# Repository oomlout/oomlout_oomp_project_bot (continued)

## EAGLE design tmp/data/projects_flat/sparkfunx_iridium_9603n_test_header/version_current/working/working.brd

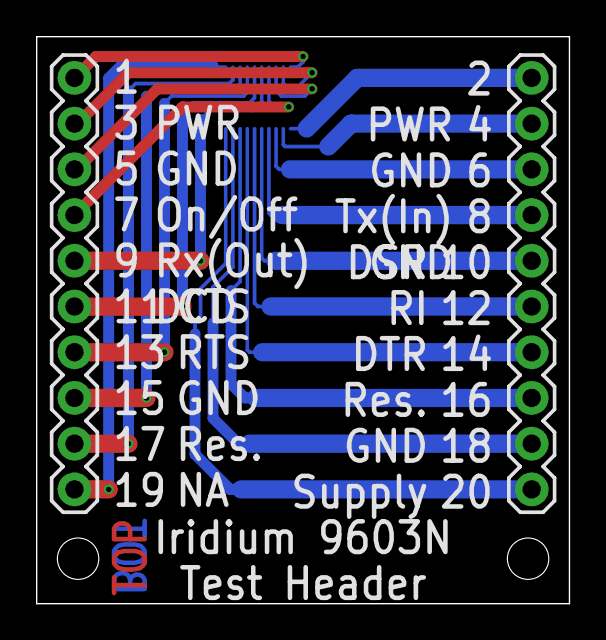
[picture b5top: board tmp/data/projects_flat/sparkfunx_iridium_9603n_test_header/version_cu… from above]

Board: 2 copper layers, 29.6 x 31.5 mm, 3 parts (1 on the bottom side), 20 nets.

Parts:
J1, J2: 1X10
J3: ST4-10-X.XX-X-D

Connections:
unnamed: J1.1, J3.1
unnamed: J2.1, J3.2
unnamed: J1.2, J3.3
unnamed: J2.2, J3.4
unnamed: J1.3, J3.5
unnamed: J2.3, J3.6
unnamed: J1.4, J3.7
unnamed: J2.4, J3.8
unnamed: J1.5, J3.9
unnamed: J2.5, J3.10
unnamed: J1.6, J3.11
unnamed: J2.6, J3.12
unnamed: J1.7, J3.13
unnamed: J2.7, J3.14
unnamed: J1.8, J3.15
unnamed: J2.8, J3.16
unnamed: J1.9, J3.17
unnamed: J2.9, J3.18
unnamed: J1.10, J3.19
unnamed: J2.10, J3.20

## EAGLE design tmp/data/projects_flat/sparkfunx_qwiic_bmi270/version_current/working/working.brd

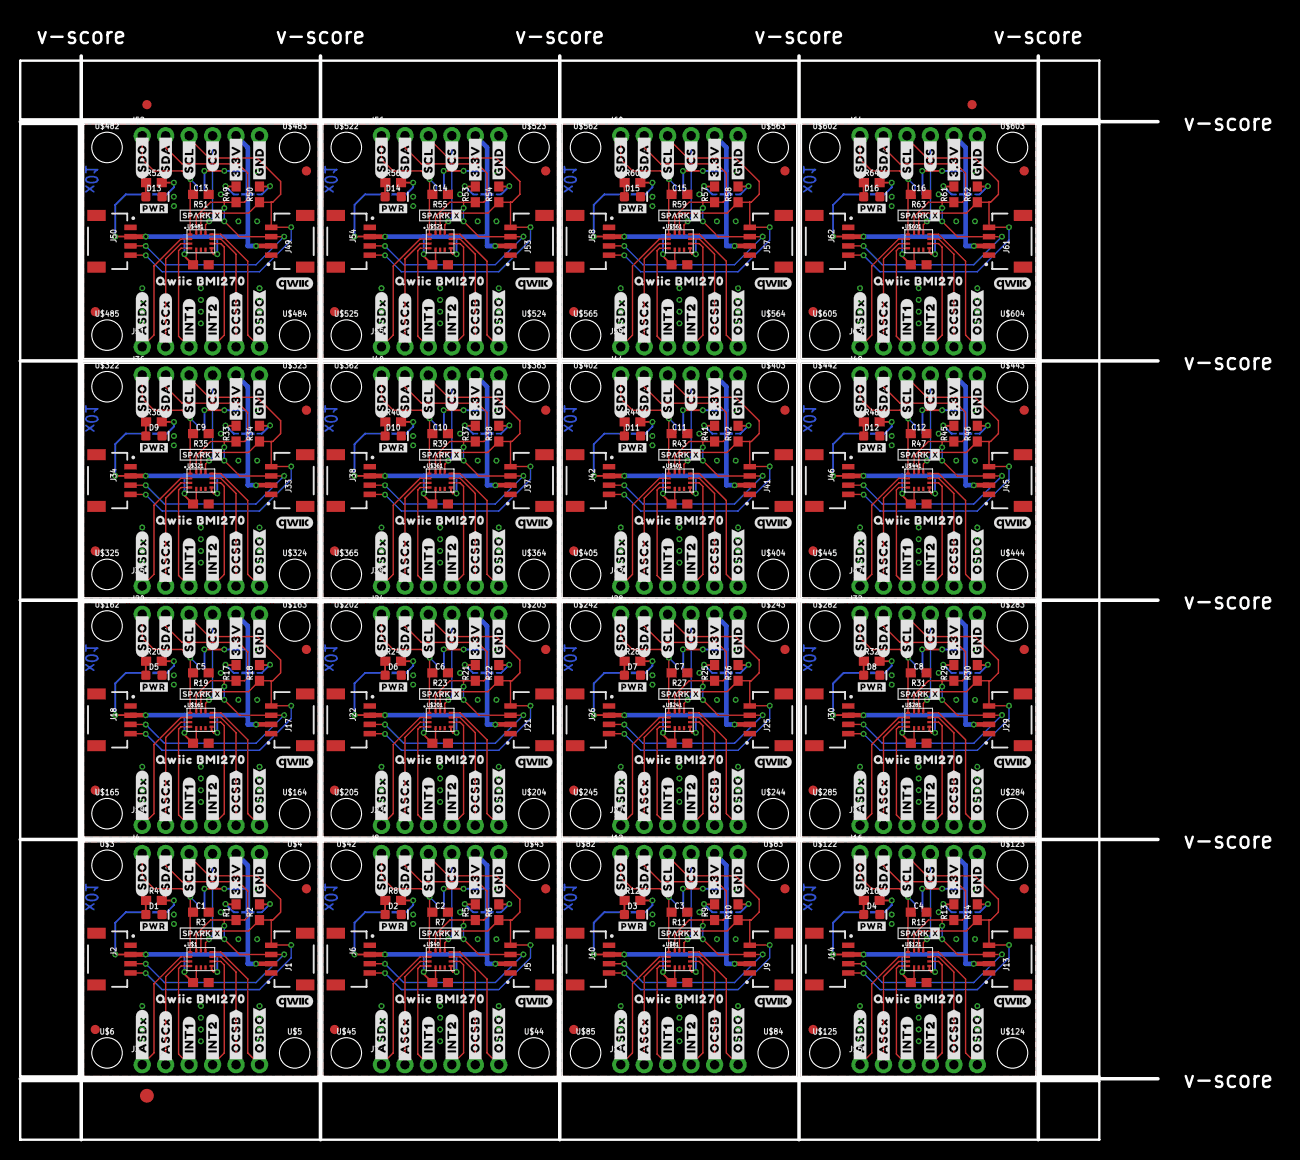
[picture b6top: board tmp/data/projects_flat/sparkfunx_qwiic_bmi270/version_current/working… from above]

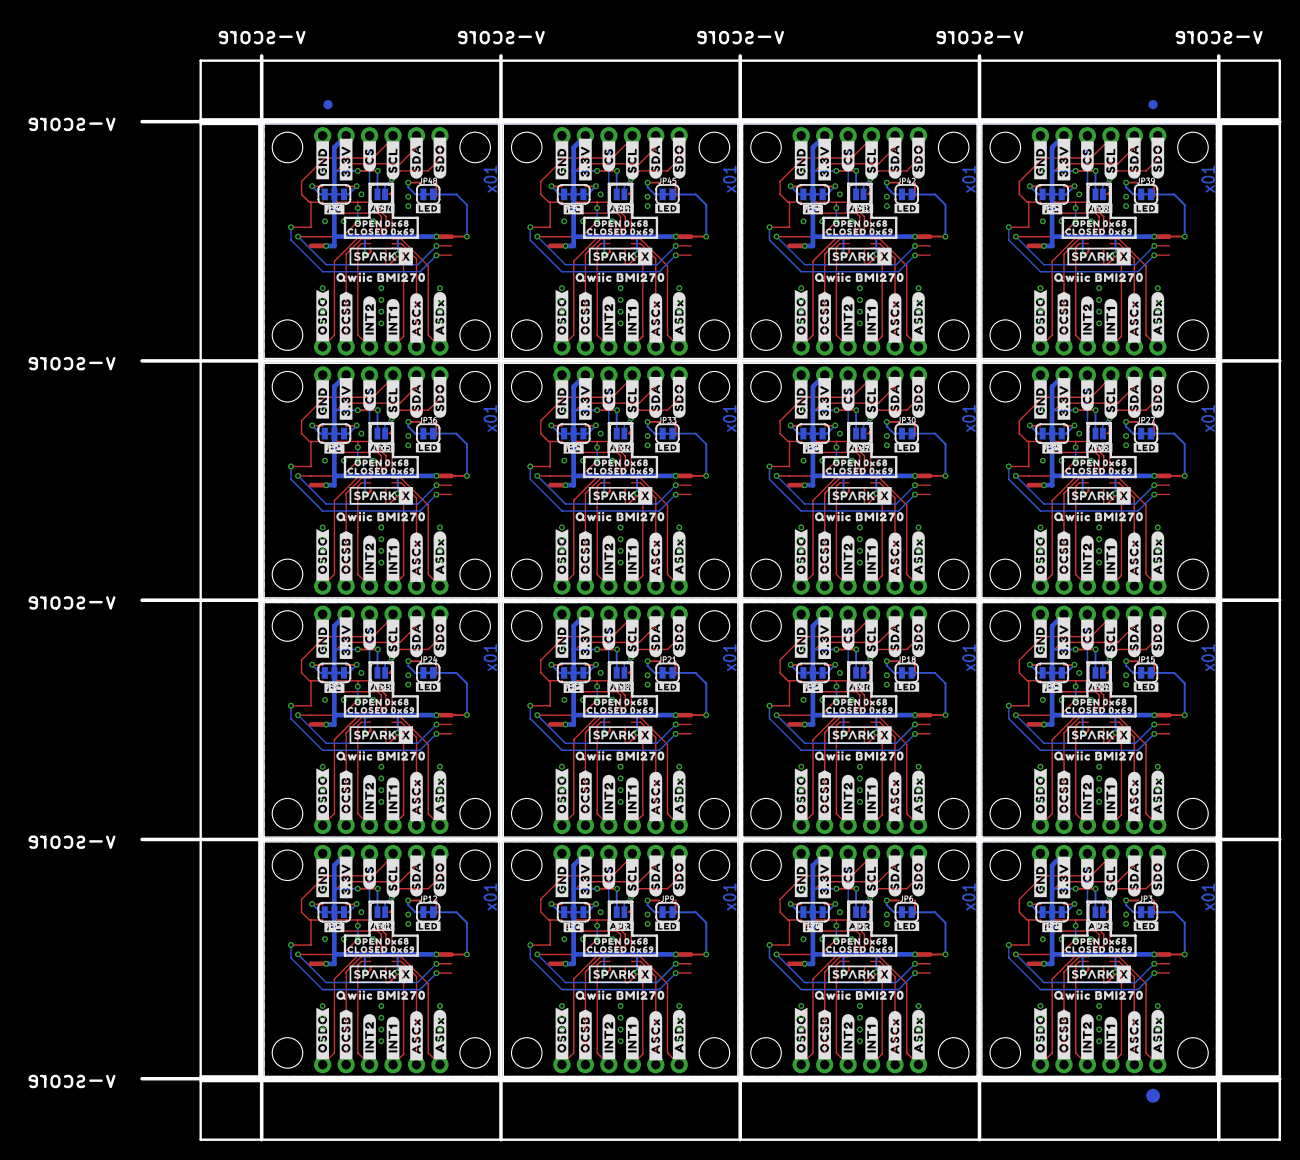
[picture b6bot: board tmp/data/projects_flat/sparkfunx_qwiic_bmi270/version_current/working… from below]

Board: 2 copper layers, 123.2 x 117.3 mm, 902 parts (355 on the bottom side), 256 nets.

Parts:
C1, C2, C3, C4, C5, C6, C7, C8, C9, C10, C11, C12, C13, C14, C15, C16: 0.1uF; 0603
D1, D2, D3, D4, D5, D6, D7, D8, D9, D10, D11, D12, D13, D14, D15, D16: RED; LED-0603
E$1, E$2, E$3, E$4: FIDUCIAL-1X2
E$5, E$6: FIDUCIAL-1.5X3
FD1, FD2, FD3, FD4, FD5, FD6, FD7, FD8, FD9, FD10, FD11, FD12, FD13, FD14, FD15, FD16, FD17, FD18, FD19, FD20, FD21, FD22, FD23, FD24, FD25, FD26, FD27, FD28, FD29, FD30, FD31, FD32: FIDUCIAL1X2; FIDUCIAL-1X2
FRAME1, FRAME2, FRAME3, FRAME4, FRAME5, FRAME6, FRAME7, FRAME8, FRAME9, FRAME10, FRAME11, FRAME12, FRAME13, FRAME14, FRAME15, FRAME16: FRAME-LETTERNO_PACKAGE; DUMMY
J1, J2, J5, J6, J9, J10, J13, J14, J17, J18, J21, J22, J25, J26, J29, J30, J33, J34, J37, J38, J41, J42, J45, J46, J49, J50, J53, J54, J57, J58, J61, J62: QWIIC_RIGHT_ANGLE; JST04_1MM_RA
J3, J4, J7, J8, J11, J12, J15, J16, J19, J20, J23, J24, J27, J28, J31, J32, J35, J36, J39, J40, J43, J44, J47, J48, J51, J52, J55, J56, J59, J60, J63, J64: 1X06_NO_SILK
JP1, JP4, JP7, JP10, JP13, JP16, JP19, JP22, JP25, JP28, JP31, JP34, JP37, JP40, JP43, JP46: JUMPER-SMT_3_2-NC_TRACE_SILK; SMT-JUMPER_3_2-NC_TRACE_SILK
JP2, JP5, JP8, JP11, JP14, JP17, JP20, JP23, JP26, JP29, JP32, JP35, JP38, JP41, JP44, JP47: JUMPER-SMT_2_NO_SILK; SMT-JUMPER_2_NO_SILK
JP3, JP6, JP9, JP12, JP15, JP18, JP21, JP24, JP27, JP30, JP33, JP36, JP39, JP42, JP45, JP48: JUMPER-SMT_2_NC_TRACE_SILK; SMT-JUMPER_2_NC_TRACE_SILK
R1, R2, R5, R6, R9, R10, R13, R14, R17, R18, R21, R22, R25, R26, R29, R30, R33, R34, R37, R38, R41, R42, R45, R46, R49, R50, R53, R54, R57, R58, R61, R62: 2.2k; 0603
R3, R7, R11, R15, R19, R23, R27, R31, R35, R39, R43, R47, R51, R55, R59, R63: 10k; 0603
R4, R8, R12, R16, R20, R24, R28, R32, R36, R40, R44, R48, R52, R56, R60, R64: 1k; 0603
U$1, U$40, U$81, U$121, U$161, U$201, U$241, U$281, U$321, U$361, U$401, U$441, U$481, U$521, U$561, U$601: BMI270
U$2, U$35, U$46, U$75, U$86, U$115, U$126, U$155, U$166, U$195, U$206, U$235, U$246, U$275, U$286, U$315, U$326, U$355, U$366, U$395, U$406, U$435, U$446, U$475, U$486, U$515, U$526, U$555, U$566, U$595, U$606, U$635: #3#3V_#4
U$3, U$4, U$5, U$6, U$42, U$43, U$44, U$45, U$82, U$83, U$84, U$85, U$122, U$123, U$124, U$125, U$162, U$163, U$164, U$165, U$202, U$203, U$204, U$205, U$242, U$243, U$244, U$245, U$282, U$283, U$284, U$285, U$322, U$323, U$324, U$325, U$362, U$363, U$364, U$365, U$402, U$403, U$404, U$405, U$442, U$443, U$444, U$445, U$482, U$483, U$484, U$485, U$522, U$523, U$524, U$525, U$562, U$563, U$564, U$565, U$602, U$603, U$604, U$605: STAND-OFF
U$7, U$34, U$47, U$74, U$87, U$114, U$127, U$154, U$167, U$194, U$207, U$234, U$247, U$274, U$287, U$314, U$327, U$354, U$367, U$394, U$407, U$434, U$447, U$474, U$487, U$514, U$527, U$554, U$567, U$594, U$607, U$634: #GND_#4
U$8, U$36, U$48, U$76, U$88, U$116, U$128, U$156, U$168, U$196, U$208, U$236, U$248, U$276, U$288, U$316, U$328, U$356, U$368, U$396, U$408, U$436, U$448, U$476, U$488, U$516, U$528, U$556, U$568, U$596, U$608, U$636: #CS_#3
U$9, U$37, U$49, U$77, U$89, U$117, U$129, U$157, U$169, U$197, U$209, U$237, U$249, U$277, U$289, U$317, U$329, U$357, U$369, U$397, U$409, U$437, U$449, U$477, U$489, U$517, U$529, U$557, U$569, U$597, U$609, U$637: #SCL_#2
U$10, U$38, U$50, U$78, U$90, U$118, U$130, U$158, U$170, U$198, U$210, U$238, U$250, U$278, U$290, U$318, U$330, U$358, U$370, U$398, U$410, U$438, U$450, U$478, U$490, U$518, U$530, U$558, U$570, U$598, U$610, U$638: #SDA_#1
U$11, U$39, U$51, U$79, U$91, U$119, U$131, U$159, U$171, U$199, U$211, U$239, U$251, U$279, U$291, U$319, U$331, U$359, U$371, U$399, U$411, U$439, U$451, U$479, U$491, U$519, U$531, U$559, U$571, U$599, U$611, U$639: #SDO_#0
U$12, U$28, U$52, U$68, U$92, U$108, U$132, U$148, U$172, U$188, U$212, U$228, U$252, U$268, U$292, U$308, U$332, U$348, U$372, U$388, U$412, U$428, U$452, U$468, U$492, U$508, U$532, U$548, U$572, U$588, U$612, U$628: #_OSDO#8
U$13, U$29, U$53, U$69, U$93, U$109, U$133, U$149, U$173, U$189, U$213, U$229, U$253, U$269, U$293, U$309, U$333, U$349, U$373, U$389, U$413, U$429, U$453, U$469, U$493, U$509, U$533, U$549, U$573, U$589, U$613, U$629: #_OCSB#7
U$14, U$31, U$54, U$71, U$94, U$111, U$134, U$151, U$174, U$191, U$214, U$231, U$254, U$271, U$294, U$311, U$334, U$351, U$374, U$391, U$414, U$431, U$454, U$471, U$494, U$511, U$534, U$551, U$574, U$591, U$614, U$631: #_INT1#7
U$15, U$30, U$55, U$70, U$95, U$110, U$135, U$150, U$175, U$190, U$215, U$230, U$255, U$270, U$295, U$310, U$335, U$350, U$375, U$390, U$415, U$430, U$455, U$470, U$495, U$510, U$535, U$550, U$575, U$590, U$615, U$630: #_INT2#7
U$16, U$32, U$56, U$72, U$96, U$112, U$136, U$152, U$176, U$192, U$216, U$232, U$256, U$272, U$296, U$312, U$336, U$352, U$376, U$392, U$416, U$432, U$456, U$472, U$496, U$512, U$536, U$552, U$576, U$592, U$616, U$632: #_ASCX#5
U$17, U$33, U$57, U$73, U$97, U$113, U$137, U$153, U$177, U$193, U$217, U$233, U$257, U$273, U$297, U$313, U$337, U$353, U$377, U$393, U$417, U$433, U$457, U$473, U$497, U$513, U$537, U$553, U$577, U$593, U$617, U$633: #_ASDX#6
U$18, U$58, U$98, U$138, U$178, U$218, U$258, U$298, U$338, U$378, U$418, U$458, U$498, U$538, U$578, U$618: #PWR#2711
U$19, U$26, U$59, U$66, U$99, U$106, U$139, U$146, U$179, U$186, U$219, U$226, U$259, U$266, U$299, U$306, U$339, U$346, U$379, U$386, U$419, U$426, U$459, U$466, U$499, U$506, U$539, U$546, U$579, U$586, U$619, U$626: QWIIC_BMI2709
U$20, U$60, U$100, U$140, U$180, U$220, U$260, U$300, U$340, U$380, U$420, U$460, U$500, U$540, U$580, U$620: SPARKX-TINY
U$21, U$61, U$101, U$141, U$181, U$221, U$261, U$301, U$341, U$381, U$421, U$461, U$501, U$541, U$581, U$621: #I�C#2714
U$22, U$62, U$102, U$142, U$182, U$222, U$262, U$302, U$342, U$382, U$422, U$462, U$502, U$542, U$582, U$622: #LED#2712
U$23, U$63, U$103, U$143, U$183, U$223, U$263, U$303, U$343, U$383, U$423, U$463, U$503, U$543, U$583, U$623: #ADR#2713
U$24, U$64, U$104, U$144, U$184, U$224, U$264, U$304, U$344, U$384, U$424, U$464, U$504, U$544, U$584, U$624: OPEN_0X682714
U$25, U$65, U$105, U$145, U$185, U$225, U$265, U$305, U$345, U$385, U$425, U$465, U$505, U$545, U$585, U$625: CLOSED_0X692714
U$27, U$67, U$107, U$147, U$187, U$227, U$267, U$307, U$347, U$387, U$427, U$467, U$507, U$547, U$587, U$627: SPARKX-SMALL
U$41, U$80, U$120, U$160, U$200, U$240, U$280, U$320, U$360, U$400, U$440, U$480, U$520, U$560, U$600, U$640: QWIIC_4MM

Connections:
3.3V: C1.2, J1.2, J2.2, J4.5, JP1.2, JP2.2, JP3.2, U$1.5, U$1.8
3.3V1: C2.2, J5.2, J6.2, J8.5, JP4.2, JP5.2, JP6.2, U$40.5, U$40.8
3.3V2: C3.2, J9.2, J10.2, J12.5, JP7.2, JP8.2, JP9.2, U$81.5, U$81.8
3.3V3: C4.2, J13.2, J14.2, J16.5, JP10.2, JP11.2, JP12.2, U$121.5, U$121.8
3.3V4: C5.2, J17.2, J18.2, J20.5, JP13.2, JP14.2, JP15.2, U$161.5, U$161.8
3.3V5: C6.2, J21.2, J22.2, J24.5, JP16.2, JP17.2, JP18.2, U$201.5, U$201.8
3.3V6: C7.2, J25.2, J26.2, J28.5, JP19.2, JP20.2, JP21.2, U$241.5, U$241.8
3.3V7: C8.2, J29.2, J30.2, J32.5, JP22.2, JP23.2, JP24.2, U$281.5, U$281.8
3.3V8: C9.2, J33.2, J34.2, J36.5, JP25.2, JP26.2, JP27.2, U$321.5, U$321.8
3.3V9: C10.2, J37.2, J38.2, J40.5, JP28.2, JP29.2, JP30.2, U$361.5, U$361.8
3.3V10: C11.2, J41.2, J42.2, J44.5, JP31.2, JP32.2, JP33.2, U$401.5, U$401.8
3.3V11: C12.2, J45.2, J46.2, J48.5, JP34.2, JP35.2, JP36.2, U$441.5, U$441.8
3.3V12: C13.2, J49.2, J50.2, J52.5, JP37.2, JP38.2, JP39.2, U$481.5, U$481.8
3.3V13: C14.2, J53.2, J54.2, J56.5, JP40.2, JP41.2, JP42.2, U$521.5, U$521.8
3.3V14: C15.2, J57.2, J58.2, J60.5, JP43.2, JP44.2, JP45.2, U$561.5, U$561.8
3.3V15: C16.2, J61.2, J62.2, J64.5, JP46.2, JP47.2, JP48.2, U$601.5, U$601.8
ADDR_SEL: J4.1, JP2.1, R3.2, U$1.1
ADDR_SEL1: J8.1, JP5.1, R7.2, U$40.1
ADDR_SEL2: J12.1, JP8.1, R11.2, U$81.1
ADDR_SEL3: J16.1, JP11.1, R15.2, U$121.1
ADDR_SEL4: J20.1, JP14.1, R19.2, U$161.1
ADDR_SEL5: J24.1, JP17.1, R23.2, U$201.1
ADDR_SEL6: J28.1, JP20.1, R27.2, U$241.1
ADDR_SEL7: J32.1, JP23.1, R31.2, U$281.1
ADDR_SEL8: J36.1, JP26.1, R35.2, U$321.1
ADDR_SEL9: J40.1, JP29.1, R39.2, U$361.1
ADDR_SEL10: J44.1, JP32.1, R43.2, U$401.1
ADDR_SEL11: J48.1, JP35.1, R47.2, U$441.1
ADDR_SEL12: J52.1, JP38.1, R51.2, U$481.1
ADDR_SEL13: J56.1, JP41.1, R55.2, U$521.1
ADDR_SEL14: J60.1, JP44.1, R59.2, U$561.1
ADDR_SEL15: J64.1, JP47.1, R63.2, U$601.1
ASCX: J3.2, U$1.3
ASCX1: J7.2, U$40.3
ASCX2: J11.2, U$81.3
ASCX3: J15.2, U$121.3
ASCX4: J19.2, U$161.3
ASCX5: J23.2, U$201.3
ASCX6: J27.2, U$241.3
ASCX7: J31.2, U$281.3
ASCX8: J35.2, U$321.3
ASCX9: J39.2, U$361.3
ASCX10: J43.2, U$401.3
ASCX11: J47.2, U$441.3
ASCX12: J51.2, U$481.3
ASCX13: J55.2, U$521.3
ASCX14: J59.2, U$561.3
ASCX15: J63.2, U$601.3
ASDX: J3.1, U$1.2
ASDX1: J7.1, U$40.2
ASDX2: J11.1, U$81.2
ASDX3: J15.1, U$121.2
ASDX4: J19.1, U$161.2
ASDX5: J23.1, U$201.2
ASDX6: J27.1, U$241.2
ASDX7: J31.1, U$281.2
ASDX8: J35.1, U$321.2
ASDX9: J39.1, U$361.2
ASDX10: J43.1, U$401.2
ASDX11: J47.1, U$441.2
ASDX12: J51.1, U$481.2
ASDX13: J55.1, U$521.2
ASDX14: J59.1, U$561.2
ASDX15: J63.1, U$601.2
CS: J4.4, U$1.12
CS1: J8.4, U$40.12
CS2: J12.4, U$81.12
CS3: J16.4, U$121.12
CS4: J20.4, U$161.12
CS5: J24.4, U$201.12
CS6: J28.4, U$241.12
CS7: J32.4, U$281.12
CS8: J36.4, U$321.12
CS9: J40.4, U$361.12
CS10: J44.4, U$401.12
CS11: J48.4, U$441.12
CS12: J52.4, U$481.12
CS13: J56.4, U$521.12
CS14: J60.4, U$561.12
CS15: J64.4, U$601.12
GND: C1.1, D1.C, J1.1, J2.1, J4.6, R3.1, U$1.6, U$1.7
GND1: C2.1, D2.C, J5.1, J6.1, J8.6, R7.1, U$40.6, U$40.7
GND2: C3.1, D3.C, J9.1, J10.1, J12.6, R11.1, U$81.6, U$81.7
GND3: C4.1, D4.C, J13.1, J14.1, J16.6, R15.1, U$121.6, U$121.7
GND4: C5.1, D5.C, J17.1, J18.1, J20.6, R19.1, U$161.6, U$161.7
GND5: C6.1, D6.C, J21.1, J22.1, J24.6, R23.1, U$201.6, U$201.7
GND6: C7.1, D7.C, J25.1, J26.1, J28.6, R27.1, U$241.6, U$241.7
GND7: C8.1, D8.C, J29.1, J30.1, J32.6, R31.1, U$281.6, U$281.7
GND8: C9.1, D9.C, J33.1, J34.1, J36.6, R35.1, U$321.6, U$321.7
GND9: C10.1, D10.C, J37.1, J38.1, J40.6, R39.1, U$361.6, U$361.7
GND10: C11.1, D11.C, J41.1, J42.1, J44.6, R43.1, U$401.6, U$401.7
GND11: C12.1, D12.C, J45.1, J46.1, J48.6, R47.1, U$441.6, U$441.7
GND12: C13.1, D13.C, J49.1, J50.1, J52.6, R51.1, U$481.6, U$481.7
GND13: C14.1, D14.C, J53.1, J54.1, J56.6, R55.1, U$521.6, U$521.7
GND14: C15.1, D15.C, J57.1, J58.1, J60.6, R59.1, U$561.6, U$561.7
GND15: C16.1, D16.C, J61.1, J62.1, J64.6, R63.1, U$601.6, U$601.7
INT1: J3.3, U$1.4
INT2: J3.4, U$1.9
INT3: J7.3, U$40.4
INT4: J7.4, U$40.9
INT5: J11.3, U$81.4
INT6: J11.4, U$81.9
INT7: J15.3, U$121.4
INT8: J15.4, U$121.9
INT9: J19.3, U$161.4
INT10: J19.4, U$161.9
INT11: J23.3, U$201.4
INT12: J23.4, U$201.9
INT13: J27.3, U$241.4
INT14: J27.4, U$241.9
INT15: J31.3, U$281.4
INT16: J31.4, U$281.9
INT17: J35.3, U$321.4
INT18: J35.4, U$321.9
INT19: J39.3, U$361.4
INT20: J39.4, U$361.9
INT21: J43.3, U$401.4
INT22: J43.4, U$401.9
INT23: J47.3, U$441.4
INT24: J47.4, U$441.9
INT25: J51.3, U$481.4
INT26: J51.4, U$481.9
INT27: J55.3, U$521.4
INT28: J55.4, U$521.9
INT29: J59.3, U$561.4
INT30: J59.4, U$561.9
INT31: J63.3, U$601.4
INT32: J63.4, U$601.9
unnamed: JP1.1, R1.2
unnamed: JP1.3, R2.2
unnamed: JP3.1, R4.2
unnamed: D1.A, R4.1
unnamed: JP4.1, R5.2
unnamed: JP4.3, R6.2
unnamed: JP6.1, R8.2
unnamed: D2.A, R8.1
unnamed: JP7.1, R9.2
unnamed: JP7.3, R10.2
unnamed: JP9.1, R12.2
unnamed: D3.A, R12.1
unnamed: JP10.1, R13.2
unnamed: JP10.3, R14.2
unnamed: JP12.1, R16.2
unnamed: D4.A, R16.1
unnamed: JP13.1, R17.2
unnamed: JP13.3, R18.2
unnamed: JP15.1, R20.2
unnamed: D5.A, R20.1
unnamed: JP16.1, R21.2
unnamed: JP16.3, R22.2
unnamed: JP18.1, R24.2
unnamed: D6.A, R24.1
unnamed: JP19.1, R25.2
unnamed: JP19.3, R26.2
unnamed: JP21.1, R28.2
unnamed: D7.A, R28.1
unnamed: JP22.1, R29.2
unnamed: JP22.3, R30.2
unnamed: JP24.1, R32.2
unnamed: D8.A, R32.1
unnamed: JP25.1, R33.2
unnamed: JP25.3, R34.2
unnamed: JP27.1, R36.2
unnamed: D9.A, R36.1
unnamed: JP28.1, R37.2
unnamed: JP28.3, R38.2
unnamed: JP30.1, R40.2
unnamed: D10.A, R40.1
unnamed: JP31.1, R41.2
unnamed: JP31.3, R42.2
unnamed: JP33.1, R44.2
unnamed: D11.A, R44.1
unnamed: JP34.1, R45.2
unnamed: JP34.3, R46.2
unnamed: JP36.1, R48.2
unnamed: D12.A, R48.1
unnamed: JP37.1, R49.2
unnamed: JP37.3, R50.2
unnamed: JP39.1, R52.2
unnamed: D13.A, R52.1
unnamed: JP40.1, R53.2
unnamed: JP40.3, R54.2
unnamed: JP42.1, R56.2
unnamed: D14.A, R56.1
unnamed: JP43.1, R57.2
unnamed: JP43.3, R58.2
unnamed: JP45.1, R60.2
unnamed: D15.A, R60.1
unnamed: JP46.1, R61.2
unnamed: JP46.3, R62.2
unnamed: JP48.1, R64.2
unnamed: D16.A, R64.1
OCSB: J3.5, U$1.10
OCSB1: J7.5, U$40.10
OCSB2: J11.5, U$81.10
OCSB3: J15.5, U$121.10
OCSB4: J19.5, U$161.10
OCSB5: J23.5, U$201.10
OCSB6: J27.5, U$241.10
OCSB7: J31.5, U$281.10
OCSB8: J35.5, U$321.10
OCSB9: J39.5, U$361.10
OCSB10: J43.5, U$401.10
OCSB11: J47.5, U$441.10
OCSB12: J51.5, U$481.10
OCSB13: J55.5, U$521.10
OCSB14: J59.5, U$561.10
OCSB15: J63.5, U$601.10
OSDO: J3.6, U$1.11
OSDO1: J7.6, U$40.11
OSDO2: J11.6, U$81.11
OSDO3: J15.6, U$121.11
OSDO4: J19.6, U$161.11
OSDO5: J23.6, U$201.11
OSDO6: J27.6, U$241.11
OSDO7: J31.6, U$281.11
OSDO8: J35.6, U$321.11
OSDO9: J39.6, U$361.11
OSDO10: J43.6, U$401.11
OSDO11: J47.6, U$441.11
OSDO12: J51.6, U$481.11
OSDO13: J55.6, U$521.11
OSDO14: J59.6, U$561.11
OSDO15: J63.6, U$601.11
SCL: J1.4, J2.4, J4.3, R2.1, U$1.13
SCL1: J5.4, J6.4, J8.3, R6.1, U$40.13
SCL2: J9.4, J10.4, J12.3, R10.1, U$81.13
SCL3: J13.4, J14.4, J16.3, R14.1, U$121.13
SCL4: J17.4, J18.4, J20.3, R18.1, U$161.13
SCL5: J21.4, J22.4, J24.3, R22.1, U$201.13
SCL6: J25.4, J26.4, J28.3, R26.1, U$241.13
SCL7: J29.4, J30.4, J32.3, R30.1, U$281.13
SCL8: J33.4, J34.4, J36.3, R34.1, U$321.13
SCL9: J37.4, J38.4, J40.3, R38.1, U$361.13
SCL10: J41.4, J42.4, J44.3, R42.1, U$401.13
SCL11: J45.4, J46.4, J48.3, R46.1, U$441.13
SCL12: J49.4, J50.4, J52.3, R50.1, U$481.13
SCL13: J53.4, J54.4, J56.3, R54.1, U$521.13
SCL14: J57.4, J58.4, J60.3, R58.1, U$561.13
SCL15: J61.4, J62.4, J64.3, R62.1, U$601.13
SDA: J1.3, J2.3, J4.2, R1.1, U$1.14
SDA1: J5.3, J6.3, J8.2, R5.1, U$40.14
SDA2: J9.3, J10.3, J12.2, R9.1, U$81.14
SDA3: J13.3, J14.3, J16.2, R13.1, U$121.14
SDA4: J17.3, J18.3, J20.2, R17.1, U$161.14
SDA5: J21.3, J22.3, J24.2, R21.1, U$201.14
SDA6: J25.3, J26.3, J28.2, R25.1, U$241.14
SDA7: J29.3, J30.3, J32.2, R29.1, U$281.14
SDA8: J33.3, J34.3, J36.2, R33.1, U$321.14
SDA9: J37.3, J38.3, J40.2, R37.1, U$361.14
SDA10: J41.3, J42.3, J44.2, R41.1, U$401.14
SDA11: J45.3, J46.3, J48.2, R45.1, U$441.14
SDA12: J49.3, J50.3, J52.2, R49.1, U$481.14
SDA13: J53.3, J54.3, J56.2, R53.1, U$521.14
SDA14: J57.3, J58.3, J60.2, R57.1, U$561.14
SDA15: J61.3, J62.3, J64.2, R61.1, U$601.14
